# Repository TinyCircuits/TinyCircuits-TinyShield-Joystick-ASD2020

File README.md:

# TinyCircuits TinyShield Joystick Board
# ASD2020 Rev4

The design files are located under design_files/ for the TinyCircuits ASD2020 Rev 4 PCB.  This is a TinyShield board that has two analog joysticks and two push buttons.

Format is in Cadsoft Eagle format - Eagle version 6.2 was used for the original design.

For more infomation on this, check out the product page at TinyCircuits.com:  https://tinycircuits.com/collections/sensors/products/joystick-tinyshield

#License:

Design by TinyCircuits.
All design files are released under the Creative Commons Attribution Share-Alike 3.0 License, see the following link for details: http://creativecommons.org/licenses/by-sa/3.0

All text above must be included in any redistribution or derived design

This project uses designs and concepts developed as part of the Arduino project and the LilyPad project.  The TinyCircuits design files themselves (schematics, PCB and libraries) are not directly derived from these works' design files and have been created new, however the concepts and basic architecture behind the TinyDuino and TinyLily products are derived and we thank the hard work of the organizations below for their contributions to open-source hardware:
  
Original Arduino Uno Design by Team Arduino

LilyPad Arduino Design by Leah Buechley and Sparkfun Electronics

Please support the open-source hardware community

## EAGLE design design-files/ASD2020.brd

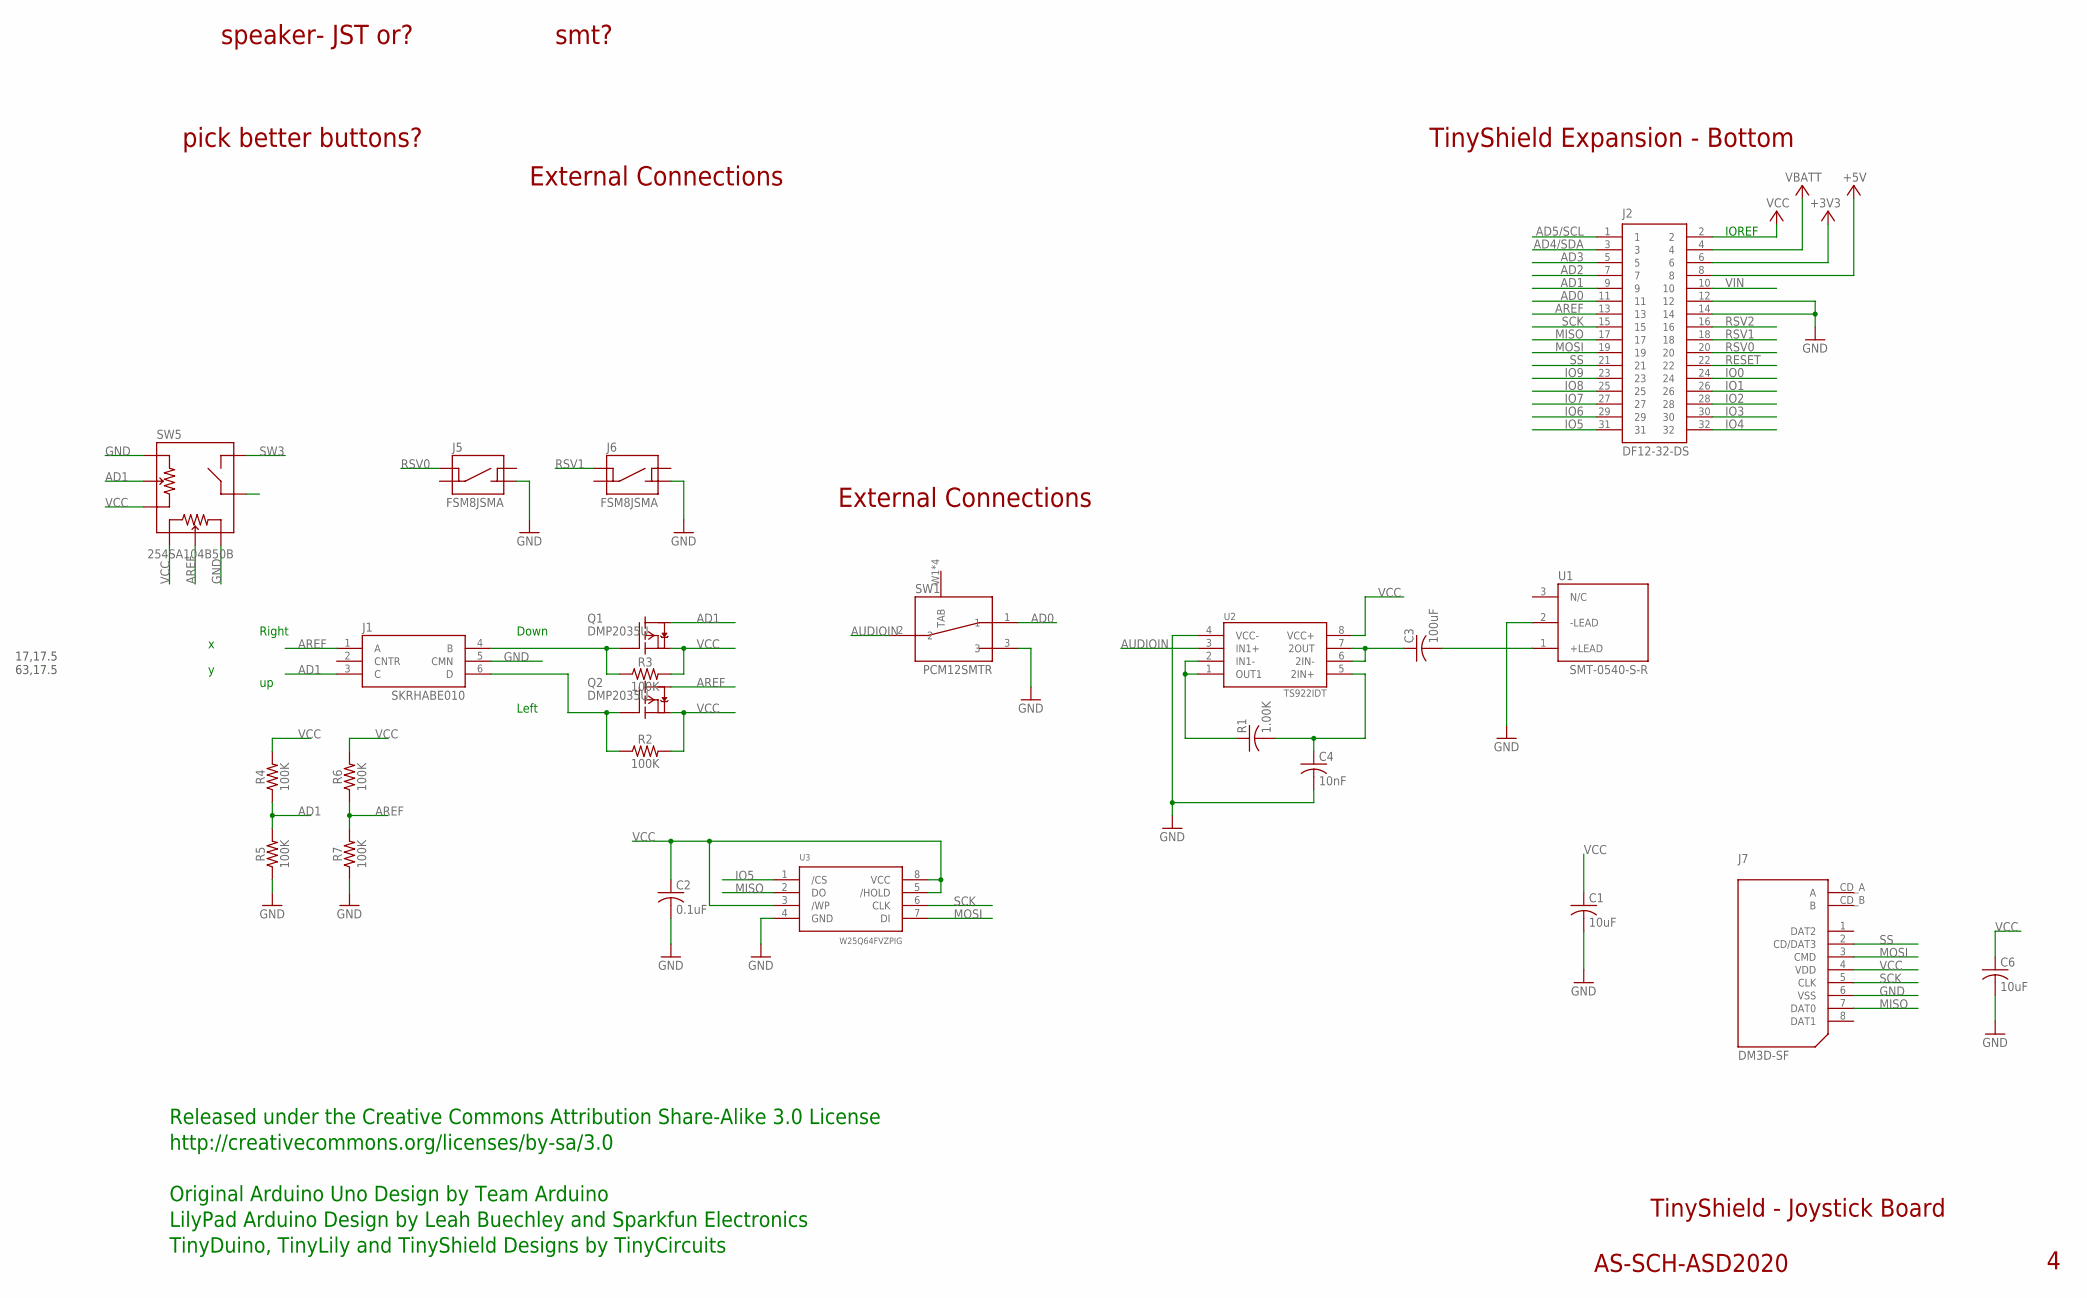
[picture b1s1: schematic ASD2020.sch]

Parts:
C1: 10uF; C0603; PARTNO AS-ITM-00002
C2: 0.1uF; C0402
C3: 100uF; C1206
C4: 10nF; C0402
C6: 10uF; C0603
J1: SKRHABE010; SKRHA
J2: DF12-32-DS; PARTNO AS-ITM-00012
J5, J6: FSM8JSMA; SWITCH-FSM/JSM
J7: DM3D-SF; SD_CARD
Q1, Q2: DMP2035U; SOT23
R1: 1.00K; C0402; PARTNO AS-ITM-00008
R2: 100K; 0402
R3, R4, R5, R6, R7: 100K; 0402; PARTNO AS-ITM-00004
SW1: PCM12SMTR
SW5: 254SA104B50B; JOYSTICK_CTS_254
U1: SMT-0540-S-R
U2: TS922IDT; SO-08-COMPACT
U3: W25Q64FVZPIG; 8-WSON-6X5

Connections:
+3V3: J2.6
+5V: J2.8
AD0: J2.11, SW1.1
AD1: J1.3 (C), J2.9, Q1.C (D), R4.1, R5.2, SW5.A2
AD2: J2.7
AD3: J2.5
AD4/SDA: J2.3
AD5/SCL: J2.1
AREF: J1.1 (A), J2.13, Q2.C (D), R6.1, R7.2, SW5.B2
AUDIOIN: SW1.2, U2.3 (IN1+)
GND: C1.2, C2.2, C4.2, C6.2, J1.5 (CMN), J2.12, J2.14, J5.P$3 (2), J6.P$3 (2), J7.6 (VSS), R5.1, R7.1, SW1.3, SW5.A1, SW5.B3, U1.2 (-LEAD), U2.4 (VCC-), U3.4 (GND)
IO0: J2.24
IO1: J2.26
IO2: J2.28
IO3: J2.30
IO4: J2.32
IO5: J2.31, U3.1 (/CS)
IO6: J2.29
IO7: J2.27
IO8: J2.25
IO9: J2.23
MISO: J2.17, J7.7 (DAT0), U3.2 (DO)
MOSI: J2.19, J7.3 (CMD), U3.7 (DI)
unnamed: C3.1, U2.6 (2IN-), U2.7 (2OUT)
unnamed: C3.2, U1.1 (+LEAD)
unnamed: C4.1, R1.2, U2.5 (2IN+)
unnamed: R1.1, U2.1 (OUT1), U2.2 (IN1-)
unnamed: J1.4 (B), Q1.B (G), R3.1
unnamed: J1.6 (D), Q2.B (G), R2.1
RESET: J2.22
RSV0: J2.20, J5.P$1 (3)
RSV1: J2.18, J6.P$1 (3)
RSV2: J2.16
SCK: J2.15, J7.5 (CLK), U3.6 (CLK)
SS: J2.21, J7.2 (CD/DAT3)
SW3: SW5.S1
VBATT: J2.4
VCC: C1.1, C2.1, C6.1, J2.2, J7.4 (VDD), Q1.E (S), Q2.E (S), R2.2, R3.2, R4.2, R6.2, SW5.A3, SW5.B1, U2.8 (VCC+), U3.3 (/WP), U3.5 (/HOLD), U3.8 (VCC)
VIN: J2.10

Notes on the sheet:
TinyShield Expansion - Bottom
TinyShield - Joystick Board
AS-SCH-ASD2020
IOREF
Released under the Creative Commons Attribution Share-Alike 3.0 License
http://creativecommons.org/licenses/by-sa/3.0
LilyPad Arduino Design by Leah Buechley and Sparkfun Electronics
TinyDuino, TinyLily and TinyShield Designs by TinyCircuits
Original Arduino Uno Design by Team Arduino
External Connections
17,17.5 63,17.5
speaker- JST or?
pick better buttons?
smt?
Right
Left
Down

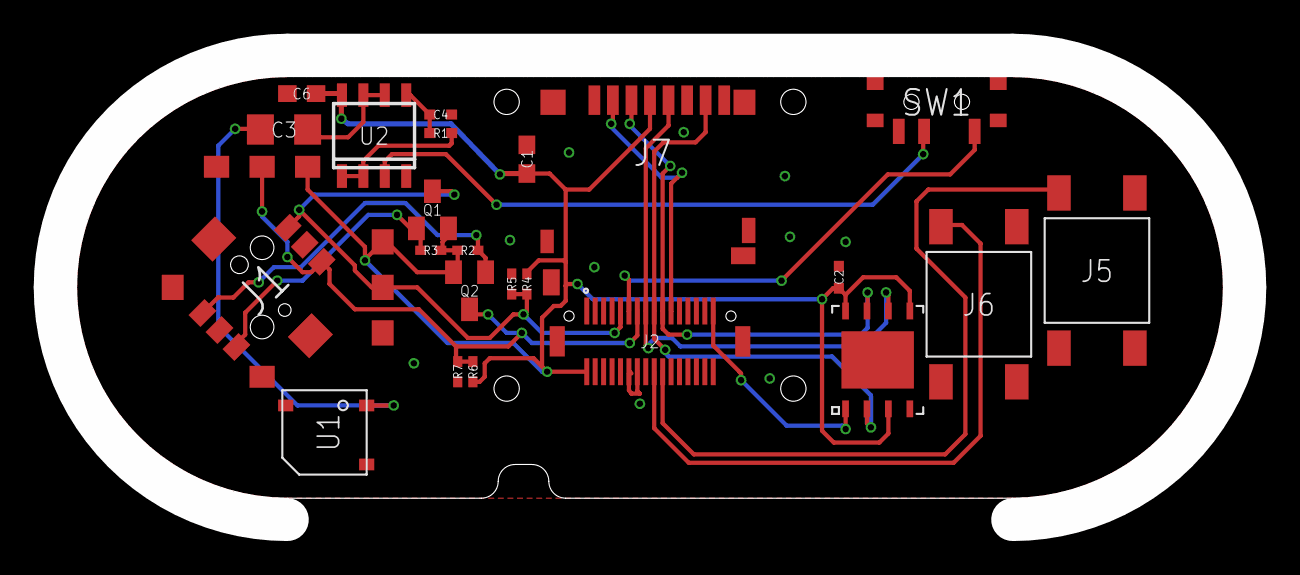
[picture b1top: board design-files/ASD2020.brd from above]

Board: 2 copper layers, 70.5 x 27.5 mm, 25 parts (0 on the bottom side), 19 nets.

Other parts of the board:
U$1: DOCFIELD-TINYCIRCUITS-PCB

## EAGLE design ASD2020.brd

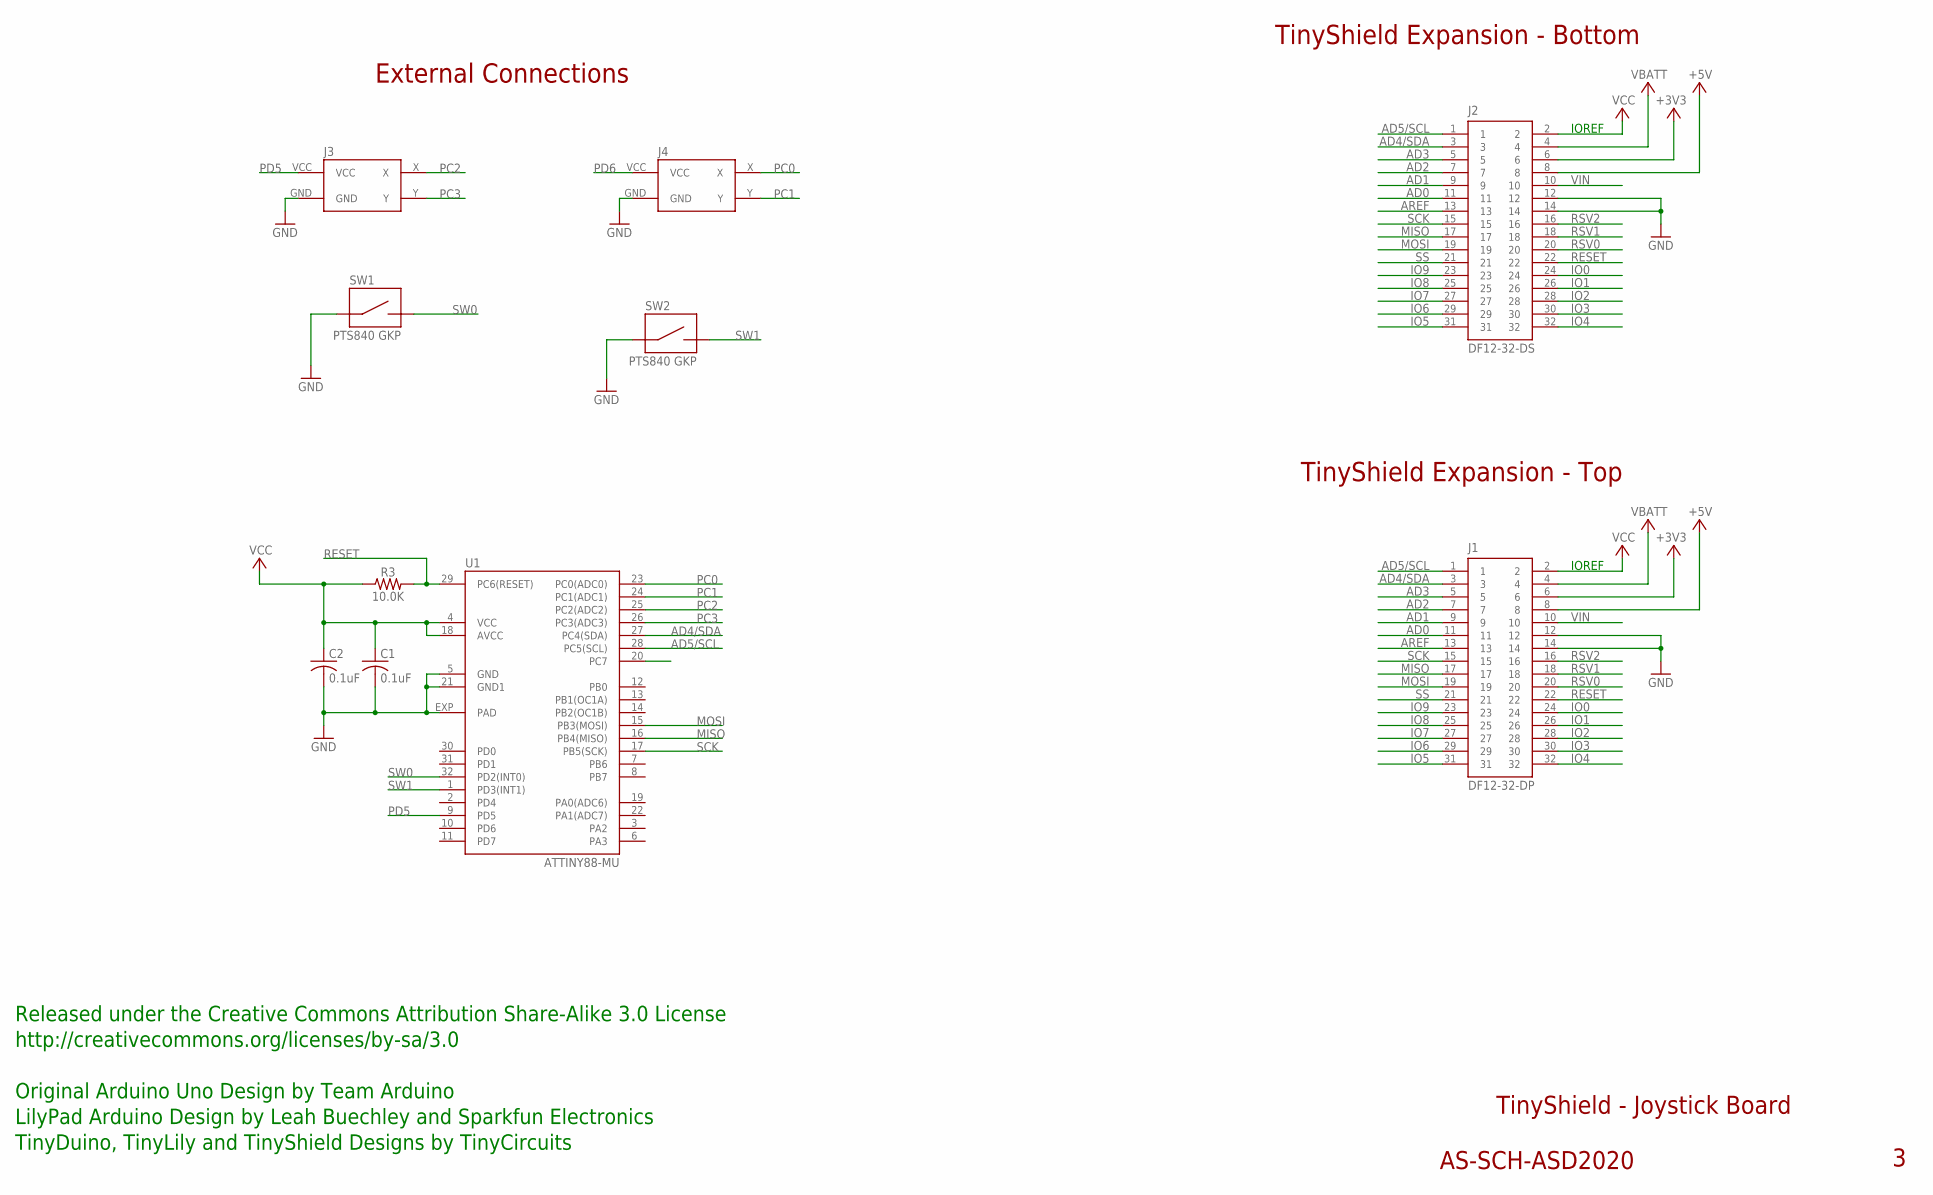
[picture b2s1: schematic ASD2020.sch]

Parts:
C1, C2: 0.1uF; C0402
J1: DF12-32-DP; PARTNO AS-ITM-00015
J2: DF12-32-DS; PARTNO AS-ITM-00012
J3, J4: AS-ITM-00235; PSPJOYSTICK
R3: 10.0K; 0402
SW1, SW2: PTS840 GKP; PTS840GKP
U1: ATTINY88-MU; ATMEL_QFN32

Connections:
+3V3: J1.6, J2.6
+5V: J1.8, J2.8
AD0: J1.11, J2.11
AD1: J1.9, J2.9
AD2: J1.7, J2.7
AD3: J1.5, J2.5
AD4/SDA: J1.3, J2.3, U1.27 (PC4(SDA))
AD5/SCL: J1.1, J2.1, U1.28 (PC5(SCL))
AREF: J1.13, J2.13
GND: C1.2, C2.2, J1.12, J1.14, J2.12, J2.14, J3.GND, J4.GND, SW1.1, SW1.2 (1), SW2.1, SW2.2 (1), U1.5 (GND), U1.21 (GND1), U1.EXP (PAD)
IO0: J1.24, J2.24
IO1: J1.26, J2.26
IO2: J1.28, J2.28
IO3: J1.30, J2.30
IO4: J1.32, J2.32
IO5: J1.31, J2.31
IO6: J1.29, J2.29
IO7: J1.27, J2.27
IO8: J1.25, J2.25
IO9: J1.23, J2.23
MISO: J1.17, J2.17, U1.16 (PB4(MISO))
MOSI: J1.19, J2.19, U1.15 (PB3(MOSI))
PC0: J4.X, U1.23 (PC0(ADC0))
PC1: J4.Y, U1.24 (PC1(ADC1))
PC2: J3.X, U1.25 (PC2(ADC2))
PC3: J3.Y, U1.26 (PC3(ADC3))
PD5: J3.VCC, U1.9 (PD5)
PD6: J4.VCC, U1.20 (PC7)
RESET: J1.22, J2.22, R3.2, U1.29 (PC6(RESET))
RSV0: J1.20, J2.20
RSV1: J1.18, J2.18
RSV2: J1.16, J2.16
SCK: J1.15, J2.15, U1.17 (PB5(SCK))
SS: J1.21, J2.21
SW0: SW1.3 (2), SW1.4 (2), U1.32 (PD2(INT0))
SW1: SW2.3 (2), SW2.4 (2), U1.1 (PD3(INT1))
VBATT: J1.4, J2.4
VCC: C1.1, C2.1, J1.2, J2.2, R3.1, U1.4 (VCC), U1.18 (AVCC)
VIN: J1.10, J2.10

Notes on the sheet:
TinyShield Expansion - Bottom
TinyShield - Joystick Board
AS-SCH-ASD2020
TinyShield Expansion - Top
IOREF
Released under the Creative Commons Attribution Share-Alike 3.0 License
http://creativecommons.org/licenses/by-sa/3.0
LilyPad Arduino Design by Leah Buechley and Sparkfun Electronics
TinyDuino, TinyLily and TinyShield Designs by TinyCircuits
Original Arduino Uno Design by Team Arduino
External Connections

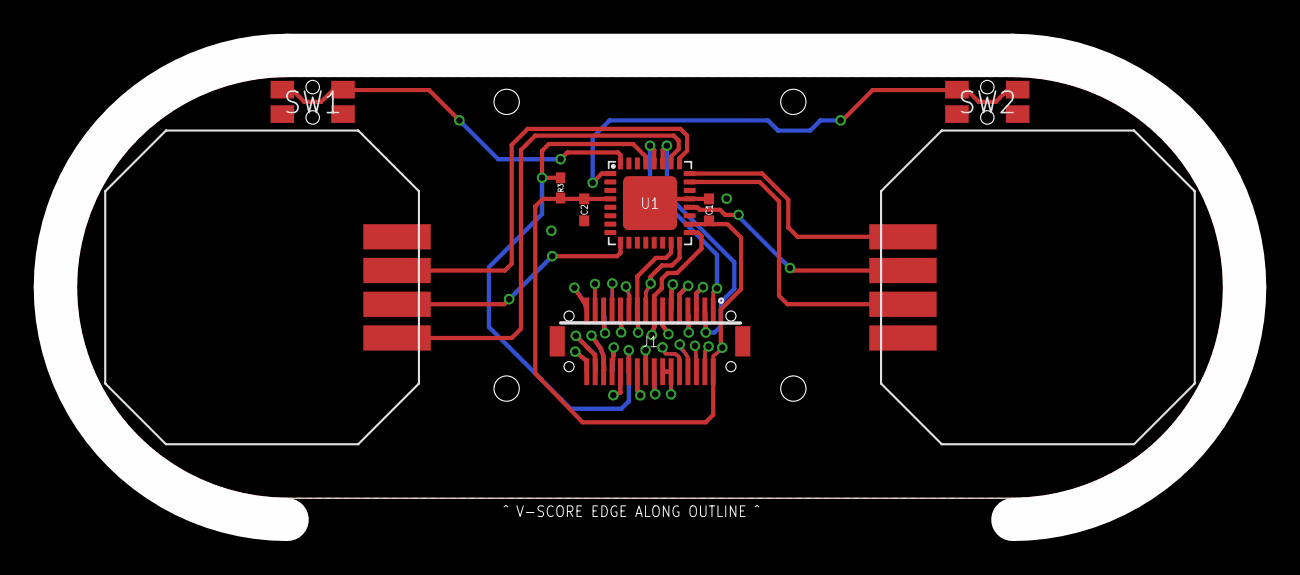
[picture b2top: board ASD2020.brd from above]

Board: 2 copper layers, 70.5 x 27.5 mm, 11 parts (1 on the bottom side), 39 nets.

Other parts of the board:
U$1: DOCFIELD-TINYCIRCUITS-PCB

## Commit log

2015-04-11 :lollipop: Added .gitattributes & .gitignore files
2019-01-02 update format
2019-01-07 updated comments
2019-04-08 Update program
2019-04-08 add zip file
